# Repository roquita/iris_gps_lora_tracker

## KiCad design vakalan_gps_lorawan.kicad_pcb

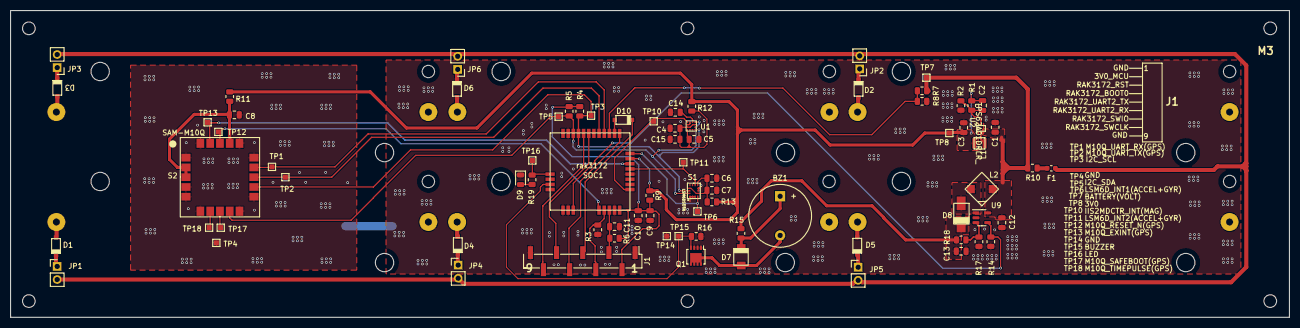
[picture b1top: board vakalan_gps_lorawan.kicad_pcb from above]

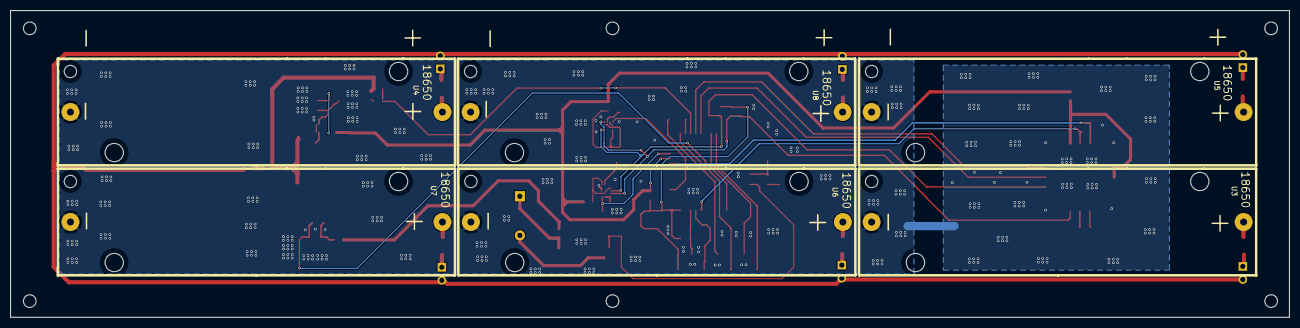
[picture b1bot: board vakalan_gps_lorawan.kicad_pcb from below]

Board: 2 copper layers, 248.3 x 59.5 mm, 85 parts (6 on the bottom side), 52 nets.

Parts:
BZ1: Buzzer; Buzzer_12x9.5RM7.6
C1, C8, C12: 4.7uF; C_0805_2012Metric
C2: 120pF; C_0805_2012Metric
C3: 22uF; C_0805_2012Metric
C4, C9: 10uF; C_0805_2012Metric
C5, C6, C7, C10, C11, C15: 0.1uF; C_0805_2012Metric
C13: 1uF; C_0805_2012Metric
C14: 220Nf; C_0805_2012Metric
D1, D2, D3, D4, D5, D6, D10: BAT54G
D7: D; FM4006
D8: D; SS14
D9: LED; LED_0805_2012Metric
F1: Fuse; Fuse_0603_1608Metric
J1: Conn_01x08_Male; PinHeader_1x09_P2.54mm_Vertical_SMD_Pin1Left
JP1, JP2, JP3, JP4, JP5, JP6: Jumper_2_Open; PinHeader_1x02_P2.54mm_Vertical
L1: 1uH; DFE252012F
L2: 10uH; CDRH4D16-100M
Q1: BUK9M11-40EX; LFPAK33
R1: 800k; R_0805_2012Metric
R2: 200k; R_0805_2012Metric
R3: 100k; R_0805_2012Metric
R4, R5, R19: 4.7k; R_0805_2012Metric
R6, R14, R16: 10k; R_0805_2012Metric
R7, R8: 2M; R_0805_2012Metric
R9, R10, R11, R12, R13, R15: 0; R_0805_2012Metric
R17: 120k; R_0805_2012Metric
R18: 1M; R_0805_2012Metric
S1: LSM6DSOTR
S2: SAM-M10Q; SAM_M10Q
SOC1: rak3172
TP1, TP2, TP3, TP4, TP5, TP6, TP7, TP8, TP10, TP11, TP12, TP13, TP14, TP15, TP16, TP17, TP18: TestPoint_Probe; TestPoint_Pad_1.0x1.0mm
U1: IIS2MDCTR
U2: TPS62A01DRLR_; TPS62A01DRLR
U3, U4, U5, U6, U7, U8: 18650
U9: AP3012; SOT-23-5

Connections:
+3V0_GPS: C8.1, R11.2, S2.2 (V_IO), S2.3 (V_BCKP), S2.17 (VCC)
+3V0_GYRACC: C6.1, C7.1, R13.2, S1.5 (VDDIO), S1.8 (VDD), S1.12 (CS)
+3V0_MAG: C4.1, C5.1, C15.1, R12.2, U1.3 (CS), U1.9 (VDD), U1.10 (VDD_IO)
+3V0_MCU: C9.1, C10.1, J1.2, R4.1, R5.1, R6.1, R9.2, SOC1.24 (VDD)
+12V: C13.1, D8.2 (K), R15.1, R18.2
+12V_BUZZER: BZ1.1 (-), D7.2 (K), R15.2
ADC_REF: C2.1, C3.1, L1.2, R1.1, R9.1, R11.1, R12.1, R13.1, SOC1.31 (ADC2), TP8.1
AP3015_SHDN: R14.1, SOC1.19 (PA8), U9.4 (~SHDN)
BATTERY: R7.2, R8.1, SOC1.3 (ADC5)
BUZZER: Q1.4 (G), R16.1, SOC1.15 (SPI1_CLK), TP15.1
GND: C1.2, C3.2, C4.2, C5.2, C6.2, C7.2, C8.2, C9.2, C10.2, C11.2, C12.2, C13.2, C14.2, C15.2, D9.1 (K), J1.1, J1.9, Q1.1 (S), Q1.2 (S), Q1.3 (S), R2.2, R3.2, R8.2, R14.2, R16.2, R17.2, S1.1 (SD0/SA0), S1.2 (SDX), S1.3 (SCX), S1.6 (GND), S1.7 (GND), S2.1 (GND), S2.4 (GND), S2.5 (GND), S2.6 (GND), S2.10 (GND), S2.11 (GND), S2.15 (GND), S2.16 (GND), S2.20 (GND), SOC1.11 (GND), SOC1.17 (GND), SOC1.18 (GND), SOC1.23 (GND), SOC1.28 (GND), TP4.1, TP14.1, U1.2 (NC), U1.6 (GND), U1.8 (GND), U1.11 (NC), U1.12 (NC), U2.1 (GND), U2.6 (PG), U3.2, U4.2, U5.2, U6.2, U7.2, U8.2, U9.2 (GND)
IIS2MDCTR_INT: SOC1.25 (ADC4), TP10.1, U1.7 (INT/DRY)
LED: R19.1, SOC1.13 (SPI1_MOSI), TP16.1
LSM6D_INT1: S1.4 (INT1), SOC1.32 (ADC1), TP6.1
LSM6D_INT2: S1.9 (INT2), SOC1.29 (PA0), TP11.1
M10Q_EXINT: S2.19 (EXINT), SOC1.30 (PB5), TP13.1
M10Q_RESET_N: S2.18 (RESET_N), SOC1.20 (PA9), TP12.1
M10Q_UART_RX: S2.14 (RXD), SOC1.4 (UART1_TX), TP1.1
M10Q_UART_TX: S2.13 (TXD), SOC1.5 (UART1_RX), TP2.1
unnamed: BZ1.2 (+), D7.1 (A), Q1.5 (D)
unnamed: C1.1, C12.1, L2.1, R7.1, R10.2, TP7.1, U2.3 (VIN), U2.4 (EN), U9.5 (IN)
unnamed: C2.2, R1.2, R2.1, U2.5 (FB)
unnamed: C14.1, U1.5 (C1)
unnamed: D1.1 (A), U3.1
unnamed: D1.2 (K), JP1.1 (A)
unnamed: D2.1 (A), U4.1
unnamed: D2.2 (K), JP2.1 (A)
unnamed: D3.1 (A), U5.1
unnamed: D3.2 (K), JP3.1 (A)
unnamed: D4.1 (A), U6.1
unnamed: D4.2 (K), JP4.1 (A)
unnamed: D5.1 (A), U7.1
unnamed: D5.2 (K), JP5.1 (A)
unnamed: D6.1 (A), U8.1
unnamed: D6.2 (K), JP6.1 (A)
unnamed: D8.1 (A), L2.2, U9.1 (SW)
unnamed: D9.2 (A), R19.2
unnamed: D10.1 (A), SOC1.2 (UART2_TX)
unnamed: F1.1, JP1.2 (B), JP2.2 (B), JP3.2 (B), JP4.2 (B), JP5.2 (B), JP6.2 (B)
unnamed: F1.2, R10.1
unnamed: L1.1, U2.2 (SW)
unnamed: R17.1, R18.1, U9.3 (FB)
unnamed: S2.7 (TIMEPULSE), TP18.1
unnamed: S2.8 (SAFEBOOT_N), TP17.1
RAK3172_BOOT0: J1.4, R3.1, SOC1.21 (BOOT)
RAK3172_RST: C11.1, J1.3, R6.2, SOC1.22 (RST)
RAK3172_SWCLK: J1.8, SOC1.8 (SWCLK)
RAK3172_SWIO: J1.7, SOC1.7 (SWIO)
RAK3172_UART2_RX: J1.6, SOC1.1 (UART2_RX)
RAK3172_UART2_TX: D10.2 (K), J1.5
SCL: R4.2, S1.13 (SCL), S2.12 (SCL), SOC1.9 (I2C_SCL), TP3.1, U1.1 (SCL/SPC)
SDA: R5.2, S1.14 (SDA), S2.9 (SDA), SOC1.10 (I2C_SDA), TP5.1, U1.4 (SDA/SDI/SDO)

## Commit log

2022-12-16 falta agregar buzzer
2022-12-16 readme.txt agregado
